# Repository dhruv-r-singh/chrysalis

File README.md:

# chrysalis

butterfly render

wing pattern

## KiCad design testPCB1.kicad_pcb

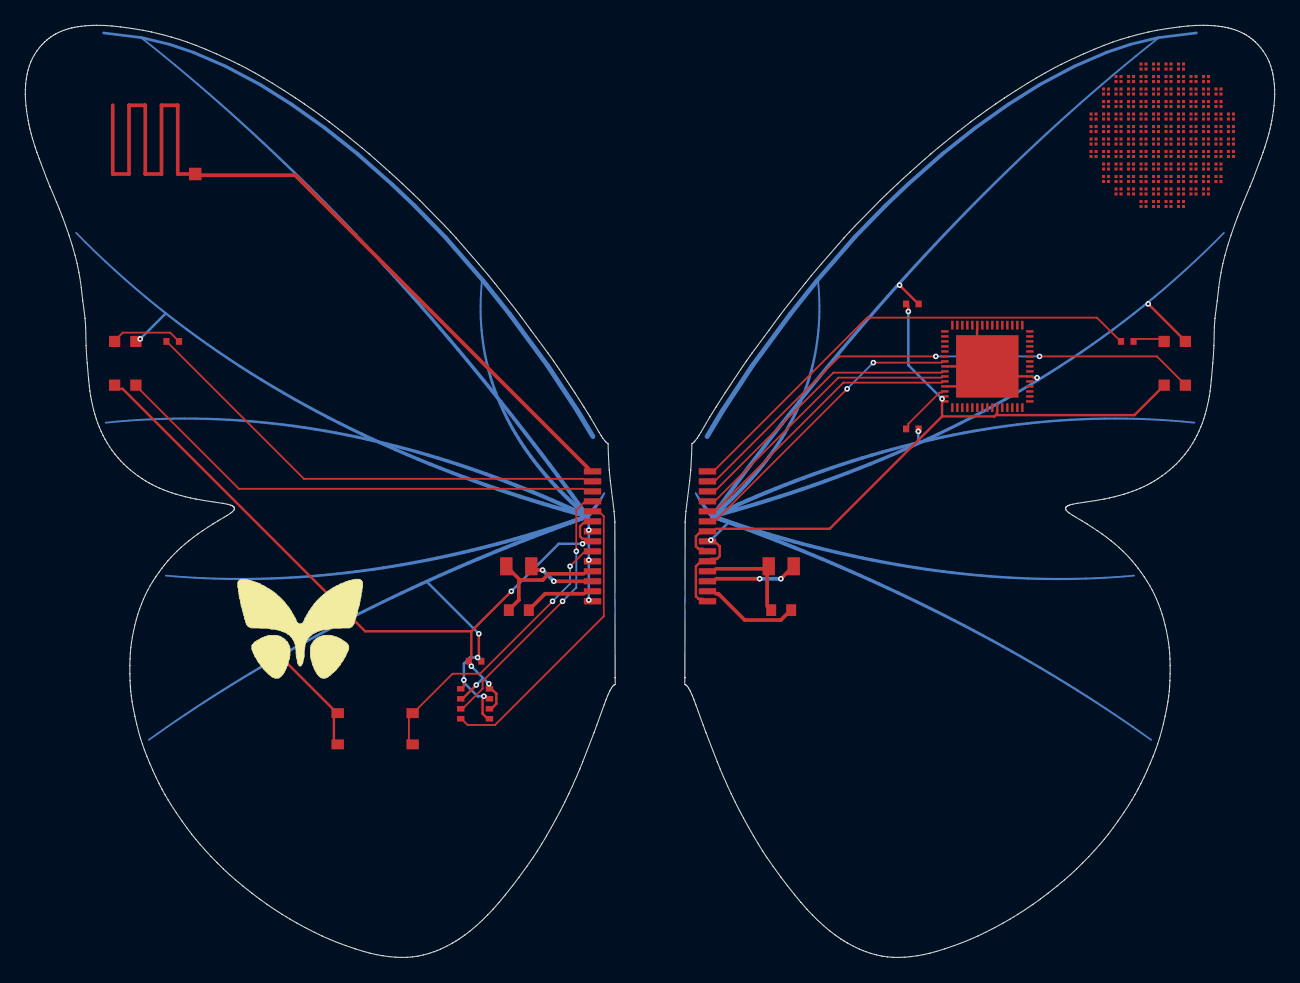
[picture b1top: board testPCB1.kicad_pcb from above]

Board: 2 copper layers, 47.2 x 74.6 mm, 131 parts (0 on the bottom side), 73 nets.

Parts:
AE1_L: ANT_FEED
C_BME_L: C_0402_1005Metric
C_VCC_R: C_0402_1005Metric
D0_4_R, D0_5_R, D0_6_R, D0_7_R, D1_2_R, D1_3_R, D1_4_R, D1_5_R, D1_6_R, D1_7_R, D1_8_R, D1_9_R, D2_1_R, D2_2_R, D2_3_R, D2_4_R, D2_5_R, D2_6_R, D2_7_R, D2_8_R, D2_9_R, D2_10_R, D3_1_R, D3_2_R, D3_3_R, D3_4_R, D3_5_R, D3_6_R, D3_7_R, D3_8_R, D3_9_R, D3_10_R, D4_0_R, D4_1_R, D4_2_R, D4_3_R, D4_4_R, D4_5_R, D4_6_R, D4_7_R, D4_8_R, D4_9_R, D4_10_R, D4_11_R, D5_0_R, D5_1_R, D5_2_R, D5_3_R, D5_4_R, D5_5_R, D5_6_R, D5_7_R, D5_8_R, D5_9_R, D5_10_R, D5_11_R, D6_0_R, D6_1_R, D6_2_R, D6_3_R, D6_4_R, D6_5_R, D6_6_R, D6_7_R, D6_8_R, D6_9_R, D6_10_R, D6_11_R, D7_0_R, D7_1_R, D7_2_R, D7_3_R, D7_4_R, D7_5_R, D7_6_R, D7_7_R, D7_8_R, D7_9_R, D7_10_R, D7_11_R, D8_1_R, D8_2_R, D8_3_R, D8_4_R, D8_5_R, D8_6_R, D8_7_R, D8_8_R, D8_9_R, D8_10_R, D9_1_R, D9_2_R, D9_3_R, D9_4_R, D9_5_R, D9_6_R, D9_7_R, D9_8_R, D9_9_R, D9_10_R, D10_2_R, D10_3_R, D10_4_R, D10_5_R, D10_6_R, D10_7_R, D10_8_R, D10_9_R, D11_4_R, D11_5_R, D11_6_R, D11_7_R: RGB_0606_PLACEHOLDER_UNVERIFIED
D_IR_L: IR_LED_0603_PLACEHOLDER
D_IR_R: IR_LED_0603_PLACEHOLDER
J1_L, J1_R: WingRoot_Strip_14
Q_IR_L: IR_PHOTOTRANSISTOR_0603_PLACEHOLDER
Q_IR_R: IR_PHOTOTRANSISTOR_0603_PLACEHOLDER
R1_L, R1_R: R_0603_1608Metric
R2_L, R2_R: R_0805_2012Metric
R_EXT_R: R_0402_1005Metric
R_IR_L: R_0402_1005Metric
R_IR_R: R_0402_1005Metric
SW1_L: TS18-5-15-SL-160_PLACEHOLDER_UNVERIFIED
U_GAS_L: BME688_LGA8_PLACEHOLDER_UNVERIFIED
U_LED_R: QFN-60_7x7_IS31FL3741_PLACEHOLDER_UNVERIFIED

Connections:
ANT_L: AE1_L.1, J1_L.1
BTN_L: J1_L.9, SW1_L.3, SW1_L.4
COL0B_R: D4_0_R.4, D5_0_R.4, D6_0_R.4, D7_0_R.4
COL0G_R: D4_0_R.3, D5_0_R.3, D6_0_R.3, D7_0_R.3
COL0R_R: D4_0_R.2, D5_0_R.2, D6_0_R.2, D7_0_R.2
COL1B_R: D2_1_R.4, D3_1_R.4, D4_1_R.4, D5_1_R.4, D6_1_R.4, D7_1_R.4, D8_1_R.4, D9_1_R.4
COL1G_R: D2_1_R.3, D3_1_R.3, D4_1_R.3, D5_1_R.3, D6_1_R.3, D7_1_R.3, D8_1_R.3, D9_1_R.3
COL1R_R: D2_1_R.2, D3_1_R.2, D4_1_R.2, D5_1_R.2, D6_1_R.2, D7_1_R.2, D8_1_R.2, D9_1_R.2
COL2B_R: D1_2_R.4, D2_2_R.4, D3_2_R.4, D4_2_R.4, D5_2_R.4, D6_2_R.4, D7_2_R.4, D8_2_R.4, D9_2_R.4, D10_2_R.4
COL2G_R: D1_2_R.3, D2_2_R.3, D3_2_R.3, D4_2_R.3, D5_2_R.3, D6_2_R.3, D7_2_R.3, D8_2_R.3, D9_2_R.3, D10_2_R.3
COL2R_R: D1_2_R.2, D2_2_R.2, D3_2_R.2, D4_2_R.2, D5_2_R.2, D6_2_R.2, D7_2_R.2, D8_2_R.2, D9_2_R.2, D10_2_R.2
COL3B_R: D1_3_R.4, D2_3_R.4, D3_3_R.4, D4_3_R.4, D5_3_R.4, D6_3_R.4, D7_3_R.4, D8_3_R.4, D9_3_R.4, D10_3_R.4
COL3G_R: D1_3_R.3, D2_3_R.3, D3_3_R.3, D4_3_R.3, D5_3_R.3, D6_3_R.3, D7_3_R.3, D8_3_R.3, D9_3_R.3, D10_3_R.3
COL3R_R: D1_3_R.2, D2_3_R.2, D3_3_R.2, D4_3_R.2, D5_3_R.2, D6_3_R.2, D7_3_R.2, D8_3_R.2, D9_3_R.2, D10_3_R.2
COL4B_R: D0_4_R.4, D1_4_R.4, D2_4_R.4, D3_4_R.4, D4_4_R.4, D5_4_R.4, D6_4_R.4, D7_4_R.4, D8_4_R.4, D9_4_R.4, D10_4_R.4, D11_4_R.4
COL4G_R: D0_4_R.3, D1_4_R.3, D2_4_R.3, D3_4_R.3, D4_4_R.3, D5_4_R.3, D6_4_R.3, D7_4_R.3, D8_4_R.3, D9_4_R.3, D10_4_R.3, D11_4_R.3
COL4R_R: D0_4_R.2, D1_4_R.2, D2_4_R.2, D3_4_R.2, D4_4_R.2, D5_4_R.2, D6_4_R.2, D7_4_R.2, D8_4_R.2, D9_4_R.2, D10_4_R.2, D11_4_R.2
COL5B_R: D0_5_R.4, D1_5_R.4, D2_5_R.4, D3_5_R.4, D4_5_R.4, D5_5_R.4, D6_5_R.4, D7_5_R.4, D8_5_R.4, D9_5_R.4, D10_5_R.4, D11_5_R.4
COL5G_R: D0_5_R.3, D1_5_R.3, D2_5_R.3, D3_5_R.3, D4_5_R.3, D5_5_R.3, D6_5_R.3, D7_5_R.3, D8_5_R.3, D9_5_R.3, D10_5_R.3, D11_5_R.3
COL5R_R: D0_5_R.2, D1_5_R.2, D2_5_R.2, D3_5_R.2, D4_5_R.2, D5_5_R.2, D6_5_R.2, D7_5_R.2, D8_5_R.2, D9_5_R.2, D10_5_R.2, D11_5_R.2
COL6B_R: D0_6_R.4, D1_6_R.4, D2_6_R.4, D3_6_R.4, D4_6_R.4, D5_6_R.4, D6_6_R.4, D7_6_R.4, D8_6_R.4, D9_6_R.4, D10_6_R.4, D11_6_R.4
COL6G_R: D0_6_R.3, D1_6_R.3, D2_6_R.3, D3_6_R.3, D4_6_R.3, D5_6_R.3, D6_6_R.3, D7_6_R.3, D8_6_R.3, D9_6_R.3, D10_6_R.3, D11_6_R.3
COL6R_R: D0_6_R.2, D1_6_R.2, D2_6_R.2, D3_6_R.2, D4_6_R.2, D5_6_R.2, D6_6_R.2, D7_6_R.2, D8_6_R.2, D9_6_R.2, D10_6_R.2, D11_6_R.2
COL7B_R: D0_7_R.4, D1_7_R.4, D2_7_R.4, D3_7_R.4, D4_7_R.4, D5_7_R.4, D6_7_R.4, D7_7_R.4, D8_7_R.4, D9_7_R.4, D10_7_R.4, D11_7_R.4
COL7G_R: D0_7_R.3, D1_7_R.3, D2_7_R.3, D3_7_R.3, D4_7_R.3, D5_7_R.3, D6_7_R.3, D7_7_R.3, D8_7_R.3, D9_7_R.3, D10_7_R.3, D11_7_R.3
COL7R_R: D0_7_R.2, D1_7_R.2, D2_7_R.2, D3_7_R.2, D4_7_R.2, D5_7_R.2, D6_7_R.2, D7_7_R.2, D8_7_R.2, D9_7_R.2, D10_7_R.2, D11_7_R.2
COL8B_R: D1_8_R.4, D2_8_R.4, D3_8_R.4, D4_8_R.4, D5_8_R.4, D6_8_R.4, D7_8_R.4, D8_8_R.4, D9_8_R.4, D10_8_R.4
COL8G_R: D1_8_R.3, D2_8_R.3, D3_8_R.3, D4_8_R.3, D5_8_R.3, D6_8_R.3, D7_8_R.3, D8_8_R.3, D9_8_R.3, D10_8_R.3
COL8R_R: D1_8_R.2, D2_8_R.2, D3_8_R.2, D4_8_R.2, D5_8_R.2, D6_8_R.2, D7_8_R.2, D8_8_R.2, D9_8_R.2, D10_8_R.2
COL9B_R: D1_9_R.4, D2_9_R.4, D3_9_R.4, D4_9_R.4, D5_9_R.4, D6_9_R.4, D7_9_R.4, D8_9_R.4, D9_9_R.4, D10_9_R.4
COL9G_R: D1_9_R.3, D2_9_R.3, D3_9_R.3, D4_9_R.3, D5_9_R.3, D6_9_R.3, D7_9_R.3, D8_9_R.3, D9_9_R.3, D10_9_R.3
COL9R_R: D1_9_R.2, D2_9_R.2, D3_9_R.2, D4_9_R.2, D5_9_R.2, D6_9_R.2, D7_9_R.2, D8_9_R.2, D9_9_R.2, D10_9_R.2
COL10B_R: D2_10_R.4, D3_10_R.4, D4_10_R.4, D5_10_R.4, D6_10_R.4, D7_10_R.4, D8_10_R.4, D9_10_R.4
COL10G_R: D2_10_R.3, D3_10_R.3, D4_10_R.3, D5_10_R.3, D6_10_R.3, D7_10_R.3, D8_10_R.3, D9_10_R.3
COL10R_R: D2_10_R.2, D3_10_R.2, D4_10_R.2, D5_10_R.2, D6_10_R.2, D7_10_R.2, D8_10_R.2, D9_10_R.2
COL11B_R: D4_11_R.4, D5_11_R.4, D6_11_R.4, D7_11_R.4
COL11G_R: D4_11_R.3, D5_11_R.3, D6_11_R.3, D7_11_R.3
COL11R_R: D4_11_R.2, D5_11_R.2, D6_11_R.2, D7_11_R.2
DRV_L: J1_L.13, R1_L.2
DRV_R: J1_R.13, R1_R.2
GND_L: C_BME_L.2, D_IR_L.2, J1_L.7, J1_L.10, J1_L.14, SW1_L.1, SW1_L.2, U_GAS_L.1, U_GAS_L.5, U_GAS_L.7
GND_R: C_VCC_R.2, D_IR_R.2, J1_R.8, J1_R.10, J1_R.14, R_EXT_R.2, U_LED_R.8, U_LED_R.12, U_LED_R.36, U_LED_R.55, U_LED_R.61
INTB_R: J1_R.6, U_LED_R.7
IR_A_L: D_IR_L.1, R_IR_L.2
IR_A_R: D_IR_R.1, R_IR_R.2
IR_DRV_L: J1_L.2, R_IR_L.1
IR_DRV_R: J1_R.1, R_IR_R.1
IR_SENSE_L: J1_L.3, Q_IR_L.2
IR_SENSE_R: J1_R.2, Q_IR_R.2
PZT_A_L: J1_L.11, R1_L.1, R2_L.1
PZT_A_R: J1_R.11, R1_R.1, R2_R.1
PZT_B_L: J1_L.12, R2_L.2
PZT_B_R: J1_R.12, R2_R.2
REXT_R: R_EXT_R.1, U_LED_R.13
ROW0_R: D0_4_R.1, D0_5_R.1, D0_6_R.1, D0_7_R.1
ROW1_R: D1_2_R.1, D1_3_R.1, D1_4_R.1, D1_5_R.1, D1_6_R.1, D1_7_R.1, D1_8_R.1, D1_9_R.1
ROW2_R: D2_1_R.1, D2_2_R.1, D2_3_R.1, D2_4_R.1, D2_5_R.1, D2_6_R.1, D2_7_R.1, D2_8_R.1, D2_9_R.1, D2_10_R.1
ROW3_R: D3_1_R.1, D3_2_R.1, D3_3_R.1, D3_4_R.1, D3_5_R.1, D3_6_R.1, D3_7_R.1, D3_8_R.1, D3_9_R.1, D3_10_R.1
ROW4_R: D4_0_R.1, D4_1_R.1, D4_2_R.1, D4_3_R.1, D4_4_R.1, D4_5_R.1, D4_6_R.1, D4_7_R.1, D4_8_R.1, D4_9_R.1, D4_10_R.1, D4_11_R.1
ROW5_R: D5_0_R.1, D5_1_R.1, D5_2_R.1, D5_3_R.1, D5_4_R.1, D5_5_R.1, D5_6_R.1, D5_7_R.1, D5_8_R.1, D5_9_R.1, D5_10_R.1, D5_11_R.1
ROW6_R: D6_0_R.1, D6_1_R.1, D6_2_R.1, D6_3_R.1, D6_4_R.1, D6_5_R.1, D6_6_R.1, D6_7_R.1, D6_8_R.1, D6_9_R.1, D6_10_R.1, D6_11_R.1
ROW7_R: D7_0_R.1, D7_1_R.1, D7_2_R.1, D7_3_R.1, D7_4_R.1, D7_5_R.1, D7_6_R.1, D7_7_R.1, D7_8_R.1, D7_9_R.1, D7_10_R.1, D7_11_R.1
ROW8_R: D8_1_R.1, D8_2_R.1, D8_3_R.1, D8_4_R.1, D8_5_R.1, D8_6_R.1, D8_7_R.1, D8_8_R.1, D8_9_R.1, D8_10_R.1
ROW9_R: D9_1_R.1, D9_2_R.1, D9_3_R.1, D9_4_R.1, D9_5_R.1, D9_6_R.1, D9_7_R.1, D9_8_R.1, D9_9_R.1, D9_10_R.1
ROW10_R: D10_2_R.1, D10_3_R.1, D10_4_R.1, D10_5_R.1, D10_6_R.1, D10_7_R.1, D10_8_R.1, D10_9_R.1
ROW11_R: D11_4_R.1, D11_5_R.1, D11_6_R.1, D11_7_R.1
SCL_L: J1_L.5, U_GAS_L.4
SCL_R: J1_R.4, U_LED_R.10
SDA_L: J1_L.4, U_GAS_L.3
SDA_R: J1_R.3, U_LED_R.9
SDB_R: J1_R.5, U_LED_R.11
VCC_L: C_BME_L.1, J1_L.6, J1_L.8, Q_IR_L.1, U_GAS_L.2, U_GAS_L.6, U_GAS_L.8
VCC_R: C_VCC_R.1, J1_R.7, J1_R.9, Q_IR_R.1, U_LED_R.14, U_LED_R.15, U_LED_R.25
